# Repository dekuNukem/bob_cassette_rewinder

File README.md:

# Bob Cassette Rewinder: Hacking Detergent DRM for 98% Cost Saving

[Get Bob Rewinder](https://www.tindie.com/products/23316/) | [Official Discord](https://discord.gg/gyGFqD2vfP) | [User Manual](user_manual.md)

---

How I defeated [Bob Dishwasher](https://daan.tech/en/product/bob-mini-dishwasher/)'s detergent cartridge DRM to refill it at 1/60 of the cost of buying new.

## Get one / Discord

To get your own Bob Rewinder, [click me!](https://www.tindie.com/products/23316/)

Feel free to [join our discord](https://discord.gg/gyGFqD2vfP) for questions, discussions, and announcements.

## Introduction

Back in Jan 2021, I watched Techmoan review the [Bob Dishwasher](https://www.youtube.com/watch?v=hVup5ya0WVQ) by Daan Tech. In short, Bob is a sleek and compact countertop dishwasher with a built-in water tank that can be filled by hand, requiring no plumbing and minimal space.

He seemed to be quite impressed, mentioning its ease of setup and use. I liked the idea myself too, and ordered one soon afterwards.

It arrived after a 2-months wait, and overall I'm very happy with it. It fits on my kitchen top, has enough space for my dishes, uses a tiny amount of water, and overall works just fine. No problems.

It is also internet-connected (of course), but I never let it online. Why in the world does a dishwasher need internet anyway?

## Bob Cassettes

One of the headline features of Bob dishwasher is the [Bob Cassette](https://daan.tech/en/discover-bob-cassette/), an all-in-one detergent cartridge. Just pop it in and off you go! No need to manually measure and add detergent each wash, very convenient!

There are two types of Bob Cassettes:

### Pop Cassette

* Contains washing detergent and rinse aid

* Lasts 30 washes

### Rock’n’roll Cassette

* Contains cleaning agent and limescale remover

* Deep cleans and maintains Bob

* Should be used every 90 cycles

* Lasts 1 wash

### Advantages

Daan Tech quoted several benefits of Bob Cassettes:

* Simple to use, no need to add detergent manually every wash.

* Exact needed quantity is dispensed, less waste.

* 2-stage dispensing. Detergent first, rinse aid at later stage.

* Made from recycled plastic, and can be mailed back and reused.

## Outrageous Cost

While those points are perfectly valid and I did enjoy using the cassettes, such convenience comes with a cost, and Daan Tech is more than happy to take it off your hands. Looking at [their website](https://daan.tech/en/product/compilation-pop-rock/), a 4-pack costs £35:

With shipping and VAT added, it costs a whopping **£43 ($60) for 90 washes**! That is 48p (67c) per wash. It might not sound like much, but it quickly adds up.

Over a year of daily washes, it would have cost **£174 ($242)** in Bob cassettes alone! Imagine paying that much recurring cost for a dishwasher!

And remember its internet connectivity? Yep, the whole reason is that it can reorder more cassettes automatically when it runs low, just like those HP inkjet printers.

It is clear that Daan Tech are banking on the convenience of subscription models. I'm sure a lot of people have no problem with that, but personally, I can think of a few better uses of my £174 than on dishwasher detergents.

Another point to consider is what happens if they went bust? No more cassettes, and now you have a fancy paperweight, like so many unnecessarily-smart appliances before it.

## Alternatives

Credit where credit's due, Daan Tech didn't completely lock down the machine with Bob cassettes. Once empty, you *can* leave it there and add detergents manually. However, they strongly suggest against this, quoting a few drawbacks:

* It's a chore to measure and add them manually at each wash.

* Dosing can be tricky, as most tablets, pods, and liquids are for full-size dishwashers.

* Multi-stage dosing impossible, can't add rinse aid after main wash.

* Limescale might develop over time and damage the machine.

It is clear that this dishwasher was designed with Bob cassettes in mind, and I do enjoy their set-and-forget simplicity. That's why I made it a priority to investigate how it works.

## A Closer Look

Looking at the cassette, we can see it has a small circuit board in the middle, with 4 contacts on each side:

At the receptacle, we can see the connector for the PCB, as well as two hoses to pump out the detergent during a wash:

Notice there are only 4 wires going into the machine. Coupled with the fact that Bob needs to read the cassette to determine how many washes are left, and write to update it after a wash, I had a pretty good guess of what that mystery PCB contains.

The answer is an **I2C EEPROM**, a popular type of non-volatile memory. EEPROMs retain whatever's inside even after losing power, and are very cheap, making them perfect at holding small configuration data in embedded systems.

To settle it once and for all, I extracted the PCB from the casing by melting the plastic with a soldering iron. A bit messy, and I probably should have used a dremel, but I didn't have one.

A closer look at the PCB confirmed my suspicion:

It's simply a 24C02 EEPROM with 4.7K pull-ups on I2C lines, a bypass cap, and some diodes, probably for reverse-insertion protection.

Looking at the [datasheet](resources/FT24Cxxx.pdf), 24C02 can only hold 256 *bytes* of data, so I guess there probably isn't much going on, but we'll need to dump its contents to be sure.

## Bob the Dumper

So my plan now is to read what's inside the EEPROM. It seemed that a special connector is needed, but after rummaging around the parts bin, I found that it fits into a USB-A female socket just fine! Although I had to insulate the metal case so it won't short on the PCB contacts.

I found a leftover board from [pimping my microwave](https://github.com/dekuNukem/pimp_my_microwave), and quickly threw together a contraption to read the EEPROM:

It would just read all 256 bytes and print them over serial, and I wrote a short [Python script](/bin_dump/bob_dump.py) to save them as a `.bin` file.

Here is a quick look at whats inside a Pop cassette, with 26 washes left:

We can see that:

* Most of the EEPROM is unused (`0xff`)

* There is a UUID-like ASCII string at the beginning

* `Classique` seem indicate the cassette type

There are few other bytes here and there, I didn't know what they do, but it doesn't really matter for now. I wanted to see what changes after another wash.

So I put the cassette back, had another wash, dumped it again, and compared the difference:

Voilà, there it is! Only one byte is different at address `0xa1`, and it went down from 0x4A to 0x49 while going from 26 to 25 washes.

Doing some interpolation, it seems that byte starts from 0x4e at 30 washes, and goes down from there.

I changed it to 0x3f, which should be 15 washes, and put it back. This happened:

111 washes! Looks like they didn't do much bound checking 😅.

A bit perplexed, I tried several other values. In the end, it seems that the mapping is like this:

| Washes Left | Value @ 0xa1 |
|:-----------:|:------------:|
|      30     |     0x4e     |
|     ...     |              |
|      16     |     0x40     |
|      15     |     0x5f     |
|     ...     |              |
|      0      |     0x50     |

[Eagle-eyed user flopp](https://github.com/dekuNukem/bob_cassette_rewinder/issues/8) pointed out the value at 0xa1 is calculated as `Washes left` XOR `0x50`, thanks! Not sure why they did it like this, but anyway!

To reset the cassette to 30 washes, all I have to do is **set that byte back to 0x4e**, easy enough!

With the simple EEPROM chip, standard 0.1 inch contact spacing, one-byte counter, and no error checking, it sure seems Daan Tech didn't really try very hard!

## Now what?

It's great now that I can reset the Bob Cassette counter, but what should I refill it *with*? After all, this whole endeavor would be pointless if they really do have some secret sauce in there that can't be found anywhere else.

Of course, Daan Tech themselves sure wish you don't play around with the cassettes:

So what exactly *is* in those cassettes? Fortunately, they did provide some details in the user manual:

----

----

It's easy to see they kept things a bit vague to discourage loonies like me, but we can still extract some useful information out of it:

* Pop Cassette has two tanks

* Tank 1 contains 130mL of washing detergent, mainly Sodium Hydroxide (NaOH) and Etidronic Acid, less than 5% concentration.

* Tank 2 contains 35mL of rinsing liquid, also less than 5% concentration.

As the names suggest, detergent helps to break down grease and clean the dishes, while rinse aid reduces water streaking and improve drying performance. [Technology Connections did a video](https://www.youtube.com/watch?v=_rBO8neWw04) about this topic, so give it a watch!

I also wanted to find out how much detergent Bob actually uses at each stage of wash, so I did a express wash on Bob, and weighed the waste water at each stage. Its water usage is as follows:

* 1000mL washing

* 650mL to wash off the detergents

* 1200mL Rinsing

Overall, less than 3L of water for an entire load! Very efficient!

----

I can now calculate the **detergent** concentration:

* 130mL tank / 30 washes = 4.33mL per wash

* 4.33mL detergent per 1000mL water = **0.433% concentration, or 1:231 dilution**.

Similarly for **rinse aid**:

* 35mL tank / 30 washes = 1.17mL per wash

* 1.17mL rinse aid per 1000mL water = **0.117% concentration, or 1:855 dilution**.

## A Clean Getaway

With those information, I can begin searching for similar dishwasher liquids on the Internet.

I first tried "Concentrated Dishwasher Detergent", which returned a lot of supermarket dishwasher gel, not quite what I want. But it quickly led to something much more promising.

The magic word appears to be: **`Commercial Dishwasher Detergent & Rinse Aid`** from **Catering supplies** websites.

A quick search showed quite a few very reasonably priced 5L detergents & rinse aids:

Of course, the question now becomes *which one do I pick?* Fortunately, all chemical products in UK comes with a `Safety Data Sheet` by regulation, which contains the composition and concentration of what's inside. This way, I can compare an unknown detergent with Bob Cassette and get a rough idea of how close it is.

Looking at the cheapest detergent (top-left), [its instruction](https://www.nisbets.co.uk/jantex-dishwasher-detergent-5-litre/cf976) states:

The dilution ratio from my earlier calculation was 1:231, right in the ballpark. Looking the data sheet:

Similar composition and concentration too! Both less than 5%.

Moving on to the cheapest [rinse aid](https://www.nisbets.co.uk/jantex-dishwasher-rinse-aid-5-litre/cf977):

Again, spot on. So there you go! Perfectly good substitutes for the detergents inside Bob cassettes.

Of course, I do realize that the chemical composition might not be 100% same, at least according to the label. But those bulk detergents are for use in professional commercial kitchens, so they are unlikely to be weak stuff. And just wait until we get to the cost analysis!

-----

**UPDATE 2021-05-29:**

Another eagle-eyed user ziviossi seems to have found the exact detergents used in the Pop and R'n'R cassette, with the same UFI number.

[Pop detergent](https://heegeo.fr/370-hygiene-en-cuisine/378-lavage-et-rincage-de-la-vaisselle-en-machine/34933-.html), UFI: 9AD7-407V-T002-0TTS

[R'n'R Cleaning Agent](https://sodiscol.fr/nos-produits/fiche-produit/0/17370/desty-liquide-lavage-toutes-eaux-5kg-ecolabel-53), UFI: P7D7-M0JG-G00K-AG7Q

Click the links for more info and datasheets. [Backup copy here.](resources/offcial_detergents)

**UPDATE 2022-03-19:**

More information about the exact detergents are being investigated by **Hawk-v3**. Read about the details here:

https://github.com/dekuNukem/bob_cassette_rewinder/issues/13

-----

## Cost Showdown

Now comes the good part, let's work out how much I save by using commercial detergents.

### Detergent

* £5.99 ex-VAT, £7.2 with VAT

* 5000mL / 4.33 mL per wash = 1154 washes

* £7.20 / 1154 = £0.0062 = 0.62p per wash

### Rinse aid

* £6.29 ex-VAT, £7.60 with VAT

* 5000mL / 1.17 mL per wash = 4273 washes

* £7.60 / 4273 = £0.0018 = 0.18p per wash

----

With that, the **total cost per wash** is:

0.62p + 0.18p = **0.80p**, or **1.1 US cents**!

We know from earlier that Bob Cassettes costs **48p (67c) per wash**.

Therefore, refilling it yourself is more than **60 times cheaper**, resulting in a massive **98%** cost saving compared to buying new!

What's more, the 5L detergent can last well over **3 years** of daily wash, while the rinse aid can last almost **12 years**! Over those time you would have spent £2088 on Bob cassettes, and who knows if they will even be around then.

----

Of course, this calculation really is the best-case scenario, it didn't account for shipping of the detergents, and they might go bad before all gets used up. But even considering those possibilities, 2p per wash should be easily achievable, which is still almost 30 times cheaper. It's a no brainer to refill your Bob Cassette if you can.

## Testing it Out

I went out and bought 2 jugs of detergent and rinse aid:

I picked them up locally, so I didn't have to pay shipping. The total came to around £17.

Refilling the cassette is easy, I taped over the PCB window to prevent liquid getting in, and injected the detergents into the cassette with a syringe with blunt needle, poking through the one-way membrane. **`WARNING`**: See [this guide](user_manual.md) for more details if you plan to do it yourself.

I then popped the cassette back, as expected, Bob reads it having full 30 washes left:

I did a wash, and the resulting dishes are just as clean as before, nothing seemed different, except I'm now paying *60 times less* for the privilege! Job done!

## Bob Rewinder Board

Everything's coming together nicely! But as I will refill the cartridge frequently in the future, I do want to make a proper gadget to renew a cassette at the push of a button, instead of using the flying wire contraption earlier.

So I quickly designed a circuit board, christened **Bob Rewinder**, and hand-soldered a prototype:

Bob Rewinder simply plugs into the cassette:

Pressing the `RENEW` button will reset the EEPROM, and I can then refill and re-use the cassette for next to nothing!

## Thoughts and Conclusions

In this project, I wanted to explore the possibility of refilling and reusing Bob cassettes so I can preserve its set-and-forget convenience at a fraction of the cost.

In the process, I...

* Identified the chip inside the Bob cassette.

* Dumped the data and figured out how to reset the counter.

* Calculated Bob's detergent usage and concentration.

* Researched alternative detergent options.

* Performed cost analysis.

* Did a test run with commercial detergents.

* Designed a circuit board to easily renew the cassette.

Looking back, nothing was particularly difficult, but it did involve a lot of topics, and I learned a lot about dishwasher cycles and detergents in the process, probably more than I would have liked :)

-------

What I find ironic is, Daan Tech isn't shy about their ["positive cycle"](https://daan.tech/en/daan-positive-cycle/) of environmentally friendly practices, while having no problem selling you single-use cassettes at 60x of the price that lasts only 30 washes. The only justification is that you are *supposed* to mail them all the way back to France so they can be refilled (and of course, sold again).

If they truly wanted to cut down on single-use plastics, what's wrong with user-refillable detergent compartments like every other full-size and commercial dishwashers? That sure seem a lot less hassle than mailing plastic cartridges back-and-forth around the world.

Despite the DRM and warnings about not to refill the cassettes yourself, they even admitted themselves that the cassettes can be reused **hundreds of times**:

They also mentioned how conventional detergent plastic bottles is bad for the environment, while the cassettes themselves only last 30 washes and uses way more plastic and electronics.

The more I think of it, the more I can draw parallel between Bob cassettes and DRM-enabled inkjet cartridges, often costing more than the printer itself. It wouldn't be surprising if Daan Tech took some inspirations from there.

----

In the end, I'm glad I tamed another totally unnecessary subscription-based internet-connected "smart" device, and managed to reuse and refill the cartridge for 1/60 the cost of buying new.

By doing so, the biggest change is I no longer have to worry about using Bob at all. There used to be a constant niggle in the back of my head about getting the most out of each wash, because once it runs out, I'm in for a long wait and expensive bill. Now that the cost is so low, I find myself using it much more liberally whenever I want, often multiple times a day.

Despite my lengthy rants, I actually really like the dishwasher itself. It is quiet, water-efficient, fast, compact, looks great, requires no plumbing, and perfect for small homes. Funny how once DRM-based nickel-and-diming is out of the equation, Bob is actually excellent at its job.

## I want one too!

I have made a few extra Bob Rewinder boards, you can [get it here](https://www.tindie.com/products/23316/).

For instructions on how to use it, [click me!](user_manual.md)

## Other Stuff

I've done a few other fun projects over the years, feel free to check them out:

[duckyPad: Do-It-All Mechanical Macropad](https://github.com/dekuNukem/duckypad): A 15-key mechanical macropad with hot-swap, RGB, and sophisticated multi-line scripting.

[Pimp My Microwave](https://github.com/dekuNukem/pimp_my_microwave): Fixing my microwave by grafting an RGB mechanical keyboard to it!

[Daytripper: Hide-my-windows Laser Tripwire](https://github.com/dekuNukem/daytripper): Saves the day while you slack off!

[exixe: Miniture Nixie Tube driver module](https://github.com/dekuNukem/exixe): Eliminate the need for vintage chips and multiplexing circuits.

[From Aduino to STM32](https://github.com/dekuNukem/STM32_tutorials): A detailed tutorial to get you started with STM32 development.

[List of all my repos](https://github.com/dekuNukem?tab=repositories)

## Questions or Comments?

Please feel free to [open an issue](https://github.com/dekuNukem/bob_cassette_rewinder/issues), ask in my [discord server](https://discord.gg/gyGFqD2vfP), DM me on discord `dekuNukem#6998`, or email `dekuNukem`@`gmail`.`com` for inquires.

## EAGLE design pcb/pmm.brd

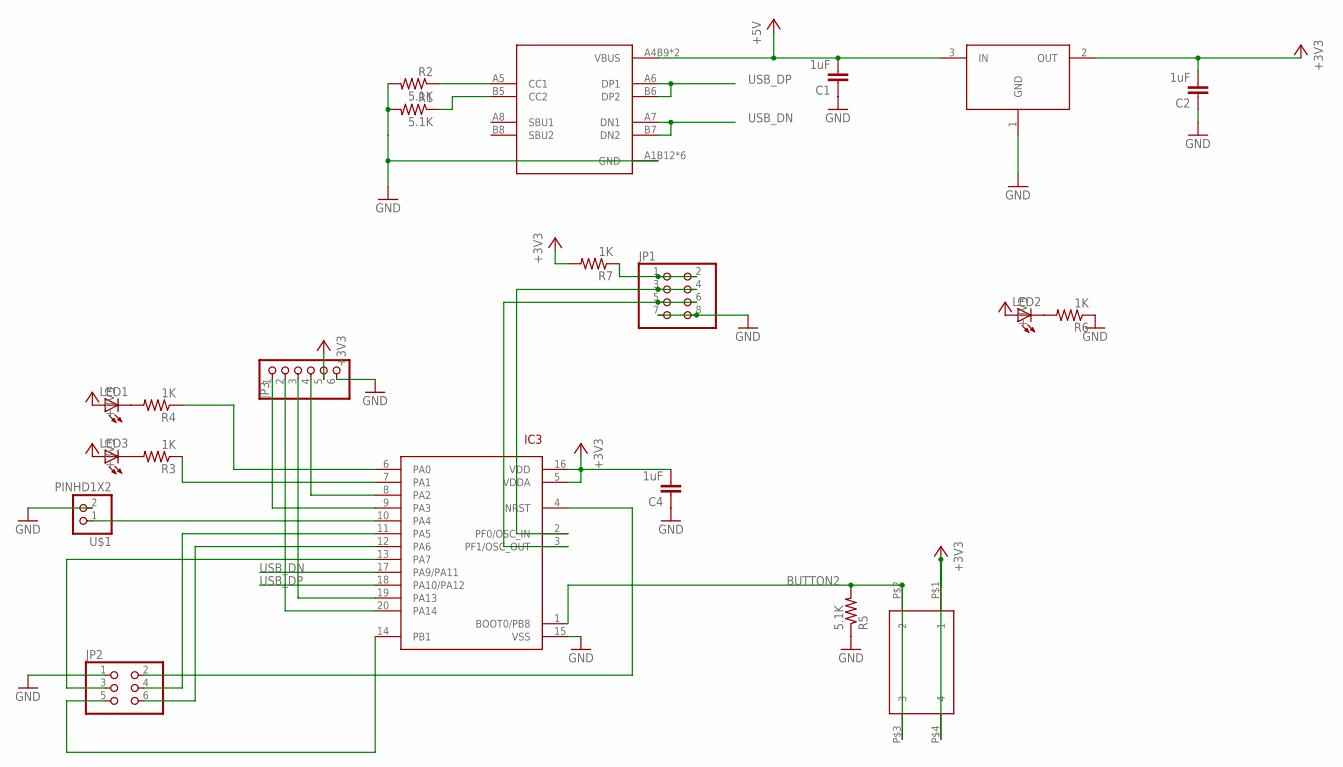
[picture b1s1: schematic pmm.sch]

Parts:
C1, C2, C4: 1uF; 0805@1
IC3: STM32F042F4; TSSOP20
JP1: PINHEAD_PINHD-2X4; PINHEAD_2X04
JP2: PINHD-2X3; 2X03
JP3: PINHD-1X6; 1X06
LED1, LED2, LED3: LEDCHIP-LED0805; CHIP-LED0805
R1, R2, R5: 5.1K; 0805
R3, R4, R6, R7: 1K; 0805
SW4: 324_SW; 342_SWICH_FOOT
U2: USBC_16P; USBC_16P_FOOT
U4: XC6206_DEV; SOT23R_INFINEON
U$1: PINHD1X2; 1X02

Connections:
+3V3: C2.2, C4.2, IC3.5 (VDDA), IC3.16 (VDD), JP3.5, LED1.A, LED2.A, LED3.A, R7.2, SW4.P$1 (1), SW4.P$4 (4), U4.2 (OUT)
+5V: C1.2, U2.A4B9 (VBUS), U2.B4A9 (VBUS), U4.3 (IN)
BUTTON2: IC3.1 (BOOT0/PB8), R5.2, SW4.P$2 (2), SW4.P$3 (3)
GND: C1.1, C2.1, C4.1, IC3.15 (VSS), JP1.7, JP1.8, JP2.1, JP3.6, R1.2, R2.2, R5.1, R6.1, U2.A1B12 (GND), U2.B11A12 (GND), U2.P$13 (GND), U2.P$14 (GND), U2.P$15 (GND), U2.P$16 (GND), U4.1 (GND), U$1.2
unnamed: LED3.C, R3.2
unnamed: IC3.2 (PF0/OSC_IN), JP1.3, JP1.4
unnamed: IC3.20 (PA14), JP3.2
unnamed: IC3.19 (PA13), JP3.3
unnamed: LED1.C, R4.2
unnamed: IC3.8 (PA2), JP3.4
unnamed: IC3.9 (PA3), JP3.1
unnamed: IC3.6 (PA0), R4.1
unnamed: IC3.7 (PA1), R3.1
unnamed: JP1.1, JP1.2, R7.1
unnamed: IC3.11 (PA5), JP2.4
unnamed: IC3.12 (PA6), JP2.6
unnamed: IC3.13 (PA7), JP2.3
unnamed: IC3.14 (PB1), JP2.5
unnamed: IC3.4 (NRST), JP2.2
unnamed: IC3.10 (PA4), U$1.1
unnamed: LED2.C, R6.2
unnamed: R1.1, U2.B5 (CC2)
unnamed: R2.1, U2.A5 (CC1)
SCL: IC3.3 (PF1/OSC_OUT), JP1.5, JP1.6
USB_DN: IC3.17 (PA9/PA11), U2.A7 (DN1), U2.B7 (DN2)
USB_DP: IC3.18 (PA10/PA12), U2.A6 (DP1), U2.B6 (DP2)

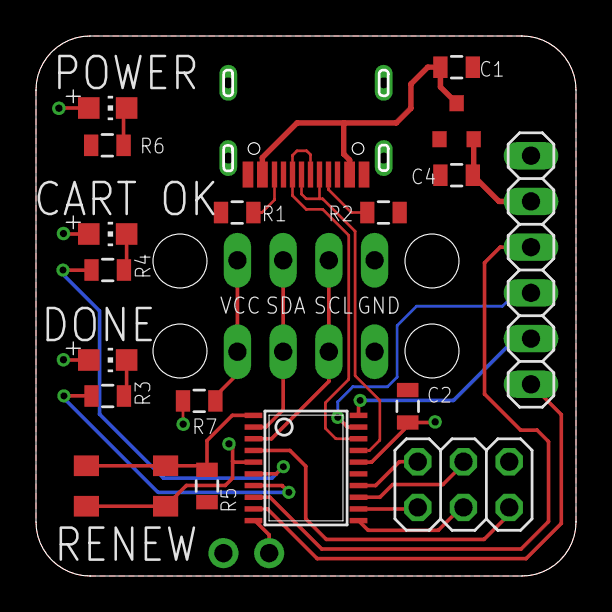
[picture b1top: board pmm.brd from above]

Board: 2 copper layers, 30.0 x 30.0 mm, 21 parts (0 on the bottom side), 26 nets.

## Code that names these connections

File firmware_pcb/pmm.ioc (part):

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Mcu.Name=STM32F042F6Px
Mcu.Package=TSSOP20
Mcu.UserName=STM32F042F6Px
PA0.GPIOParameters=PinState,GPIO_Label
PA0.GPIO_Label=LED_CARTOK
PA0.PinState=GPIO_PIN_SET
PA0.Signal=GPIO_Output
PA1.GPIOParameters=PinState,GPIO_Label
PA1.GPIO_Label=LED_DONE
PA1.PinState=GPIO_PIN_SET
PA1.Signal=GPIO_Output
PA11.Mode=Device
PA11.Signal=USB_DM
PA12.Mode=Device
PA12.Signal=USB_DP
PA13.Mode=Serial_Wire
PA13.Signal=SYS_SWDIO
PA14.Mode=Serial_Wire
PA14.Signal=SYS_SWCLK
PA2.Mode=Asynchronous
PA2.Signal=USART2_TX
PA3.Mode=Asynchronous
PA3.Signal=USART2_RX
PB8.GPIOParameters=GPIO_Label
PB8.GPIO_Label=USER_BUTTON
PB8.Signal=GPIO_Input
PF0-OSC_IN.Mode=I2C
PF0-OSC_IN.Signal=I2C1_SDA
PF1-OSC_OUT.Mode=I2C
PF1-OSC_OUT.Signal=I2C1_SCL
RCC.SYSCLKFreq_VALUE=48000000
RCC.SYSCLKSource=RCC_SYSCLKSOURCE_HSI48
board=custom

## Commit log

2021-03-14 dump done
2021-03-14 added python dump script
2021-03-17 done pcb
2021-03-28 pcb_blink
2021-03-28 usb recv working
2021-03-29 before cube
2021-03-29 before timer
2021-03-29 before dog
2021-03-29 dog working
2021-03-29 eeprom working, pc dump working, washes number figured out
2021-03-29 added out of range value observation
2021-04-01 fixed card edge connector footprint
2021-04-03 cleaned up for public repo
2021-04-03 clean up
2021-04-03 added datasheets
2021-04-03 added url to pcb
2021-04-03 firmware feature complete
2021-04-03 pc app done apart from update
2021-04-03 removed unused file
2021-04-04 added dfu file
2021-04-04 added update
2021-04-04 checked UI on macos
2021-04-04 updated component values
2021-04-04 added timeout in update checking
2021-04-09 writing up
2021-04-09 cleanup
2021-04-10 writing more
2021-04-10 fix typos
2021-04-10 writing conclusion
2021-04-10 now rewinds rock'n'roll cassettes correctly
2021-04-10 updated DFU file
2021-04-10 fixed bug
2021-04-11 almost done
2021-04-11 writing done
2021-04-12 adjust wording
2021-04-12 updated tindie links
2021-04-18 Fix typos in README
2021-04-18 Fix typos in User Manual
2021-04-19 added discord link
2021-04-28 fixed typo
2021-04-30 added store and discord link
2021-05-02 Fix link to Duckypad repo
    It's currently pointing to daytripper.
2021-05-02 Fix typo
2021-05-02 Fix off-by-10 error in one division. Update text to match.
2021-05-02 updated figures from rinse aid calculation
2021-05-02 updated figures
2021-05-02 added discovery by flopp
2021-05-02 fixed a typo
2021-05-02 fixed another typo
2021-05-29 added info about exact detergents
2021-05-29 added comments about rock'n'roll cassettes
2021-08-09 added instructions about enabling write protect
2021-08-09 finishing touches on PC app
2021-08-09 added build script
2021-08-09 added bob utility instruction
2021-08-09 updated bob utility instruction
2021-08-09 clean up instructions
2021-08-09 added firmware history
2021-08-29 docs: Fix a few typos
    There are small typos in:
    - firmware/code/Drivers/CMSIS/Include/core_cm3.h
    - firmware/code/Drivers/CMSIS/Include/core_cm4.h
    - firmware/code/Drivers/CMSIS/Include/core_cm7.h
    - firmware/code/Drivers/CMSIS/Include/core_sc300.h
    - firmware/code/Drivers/STM32F0xx_HAL_Driver/Inc/stm32f0xx_hal_dma.h
2021-12-18 minor adjustments on PCB
2022-03-19 updated detergent information
2022-05-05 Add Continuous Feed Docs.
2024-03-28 updated wording
2024-10-28 using github pages
2024-11-04 updated pcb for next production run

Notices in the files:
parts and their libraries:
SparkFun-Passives: Licensing: Creative Commons ShareAlike 4.0 International - https://creativecommons.org/licenses/by-sa/4.0
